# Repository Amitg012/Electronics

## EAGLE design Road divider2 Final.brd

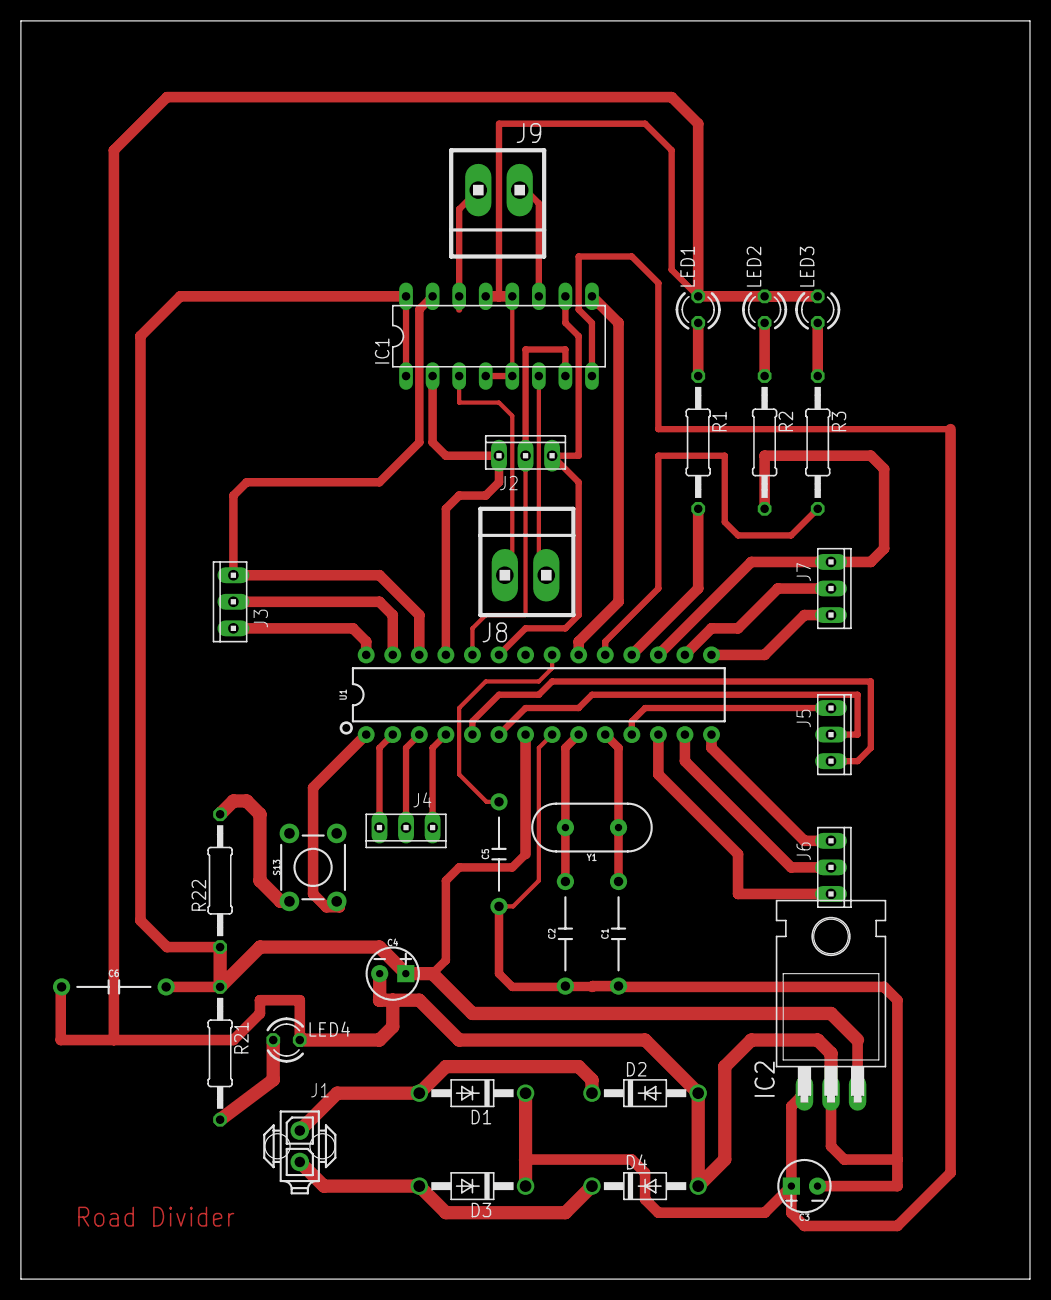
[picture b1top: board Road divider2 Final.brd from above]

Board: 2 copper layers, 96.5 x 120.3 mm, 33 parts (0 on the bottom side), 38 nets.

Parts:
C1, C2, C5, C6: 10nF; CAP-PTH-10MM
C3, C4: 10uF; CPOL-RADIAL-2.5MM-5MM-KIT
D1, D2, D3, D4: 1N4004; DO41-10
IC1: L293D; DIL16
IC2: 7812T; TO220H
J1: 794681-2
J2, J3, J4, J5, J6, J7: 10X03MTA
J8, J9: 1X2MTA
LED1, LED2, LED3, LED4: TLLR4400; LED3MM
R1, R2, R3, R21, R22: 0207/12
S13: MOMENTARY-SWITCH-SPST-PTH-6.0MM-KIT; TACTILE_SWITCH_PTH_6.0MM_KIT
U1: 328P; DIP28
Y1: 16MHz; HC49US

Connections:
5V: C4.1, C6.2, IC1.1, IC1.9, IC1.16, IC2.3, R21.1, R22.1, U1.7, U1.20
12V: C3.1, D1.C, D3.C, IC1.8, IC2.1
GND: C1.1, C2.1, C3.2, C4.2, C5.1, C6.1, D2.A, D4.A, IC1.4, IC1.5, IC1.12, IC1.13, IC2.2, LED1.K, LED2.K, LED3.K, LED4.K, U1.8, U1.22
unnamed: C5.2, U1.21
unnamed: D1.A, D2.C, J1.1
unnamed: C2.2, U1.9, Y1.2
unnamed: C1.2, U1.10, Y1.1
unnamed: LED4.A, R21.2
unnamed: R22.2, S13.1
unnamed: S13.3, U1.1
unnamed: D3.A, D4.C, J1.2
unnamed: IC1.2, J2.3, U1.25
unnamed: IC1.7, J2.2, U1.24
unnamed: IC1.10, J2.1, U1.23
unnamed: IC1.15, J3.1, U1.26
unnamed: J3.2, U1.27
unnamed: J3.3, U1.28
unnamed: J4.1, U1.2
unnamed: J4.2, U1.3
unnamed: J4.3, U1.4
unnamed: J5.1, U1.5
unnamed: J5.2, U1.6
unnamed: J5.3, U1.11
unnamed: J6.1, U1.12
unnamed: J6.2, U1.13
unnamed: J6.3, U1.14
unnamed: J7.1, U1.15
unnamed: J7.2, U1.16
unnamed: J7.3, R2.2, U1.17
unnamed: IC1.14, J9.1
unnamed: IC1.3, J8.2
unnamed: IC1.6, J8.1
unnamed: IC1.11, J9.2
unnamed: R1.2, U1.18
unnamed: R3.2, U1.19
unnamed: LED1.A, R1.1
unnamed: LED2.A, R2.1
unnamed: LED3.A, R3.1

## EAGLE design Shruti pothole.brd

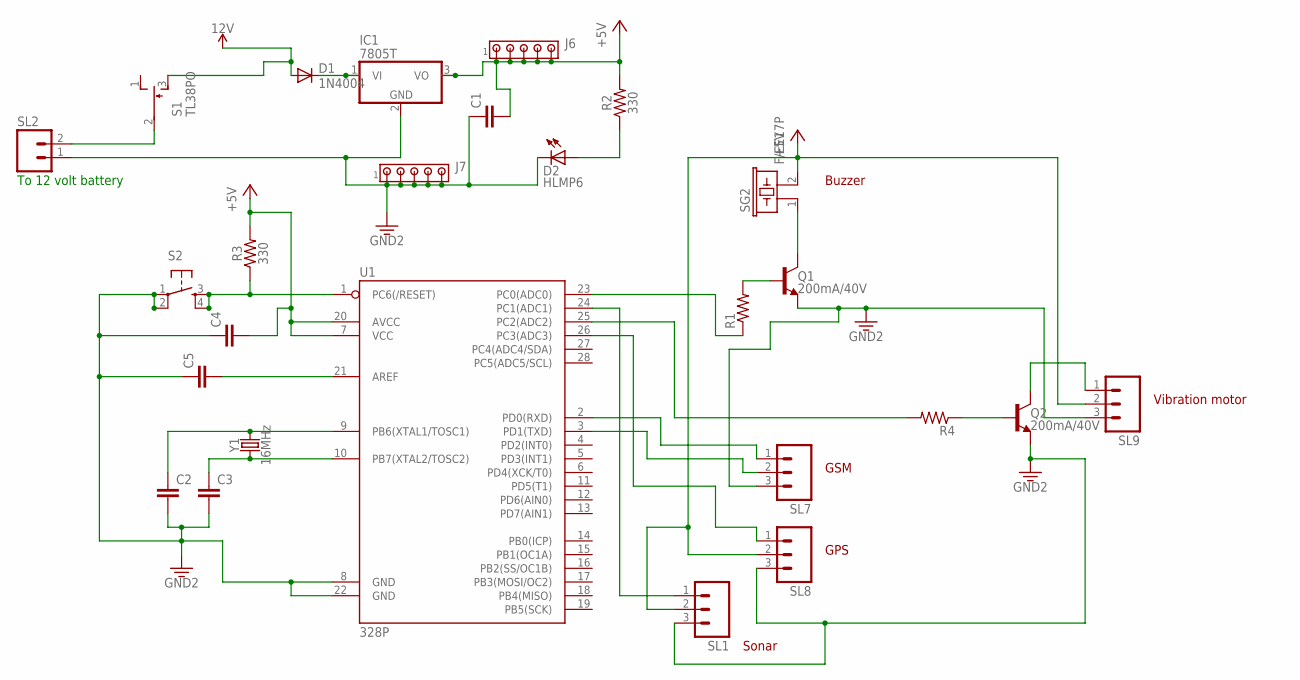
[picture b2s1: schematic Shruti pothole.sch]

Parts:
C1, C2, C3, C4, C5: C5/2.5; C5B2.5
D1: 1N4004; DO41-10
D2: HLMP6
IC1: 7805T; TO220H
J6, J7: MTA05-100; 10X05MTA
Q1, Q2: 200mA/40V; TO-92
R1, R4: R-US_0204/7; 0204/7
R2, R3: 330; AXIAL-0.3
S1: TL38PO; TL3XPO
S2: TAC_SWITCHPTH; TACTILE-PTH
SG2: F/EE17P
SL1, SL7, SL8, SL9: MA03; 03P
SL2: MA02; 02PA
U1: 328P; DIP28
Y1: 16MHz; HC49US

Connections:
3.3V: C1.1, C2.2, C3.2, C4.1, C5.1, D2.K, IC1.2 (GND), J7.1, J7.2, J7.3, J7.4, J7.5, Q1.1 (E), Q2.1 (E), S2.1, S2.2, SL1.3, SL2.1, SL7.3, SL8.3, SL9.3, U1.8 (GND), U1.22 (GND)
12V: D1.A, S1.3 (S)
+5V: C1.2, C4.2, IC1.3 (VO), J6.1, J6.2, J6.3, J6.4, J6.5, R2.P$2 (2), R3.P$2 (2), SG2.2, SL1.2, SL8.2, SL9.2, U1.7 (VCC), U1.20 (AVCC)
unnamed: Q1.3 (C), SG2.1
unnamed: SL7.1, U1.2 (PD0(RXD))
unnamed: Q1.2 (B), R1.2
unnamed: Q2.2 (B), R4.1
unnamed: SL7.2, U1.3 (PD1(TXD))
unnamed: R1.1, U1.23 (PC0(ADC0))
unnamed: D2.A, R2.P$1 (1)
unnamed: C3.1, U1.10 (PB7(XTAL2/TOSC2)), Y1.1
unnamed: SL1.1, U1.24 (PC1(ADC1))
unnamed: R3.P$1 (1), S2.3, S2.4, U1.1 (PC6(/RESET))
unnamed: R4.2, U1.25 (PC2(ADC2))
unnamed: C5.2, U1.21 (AREF)
unnamed: Q2.3 (C), SL9.1
unnamed: S1.2, SL2.2
unnamed: SL8.1, U1.26 (PC3(ADC3))
unnamed: D1.C, IC1.1 (VI)
unnamed: C2.1, U1.9 (PB6(XTAL1/TOSC1)), Y1.2

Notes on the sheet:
To 12 volt battery
Buzzer
Vibration motor
GSM
GPS
Sonar

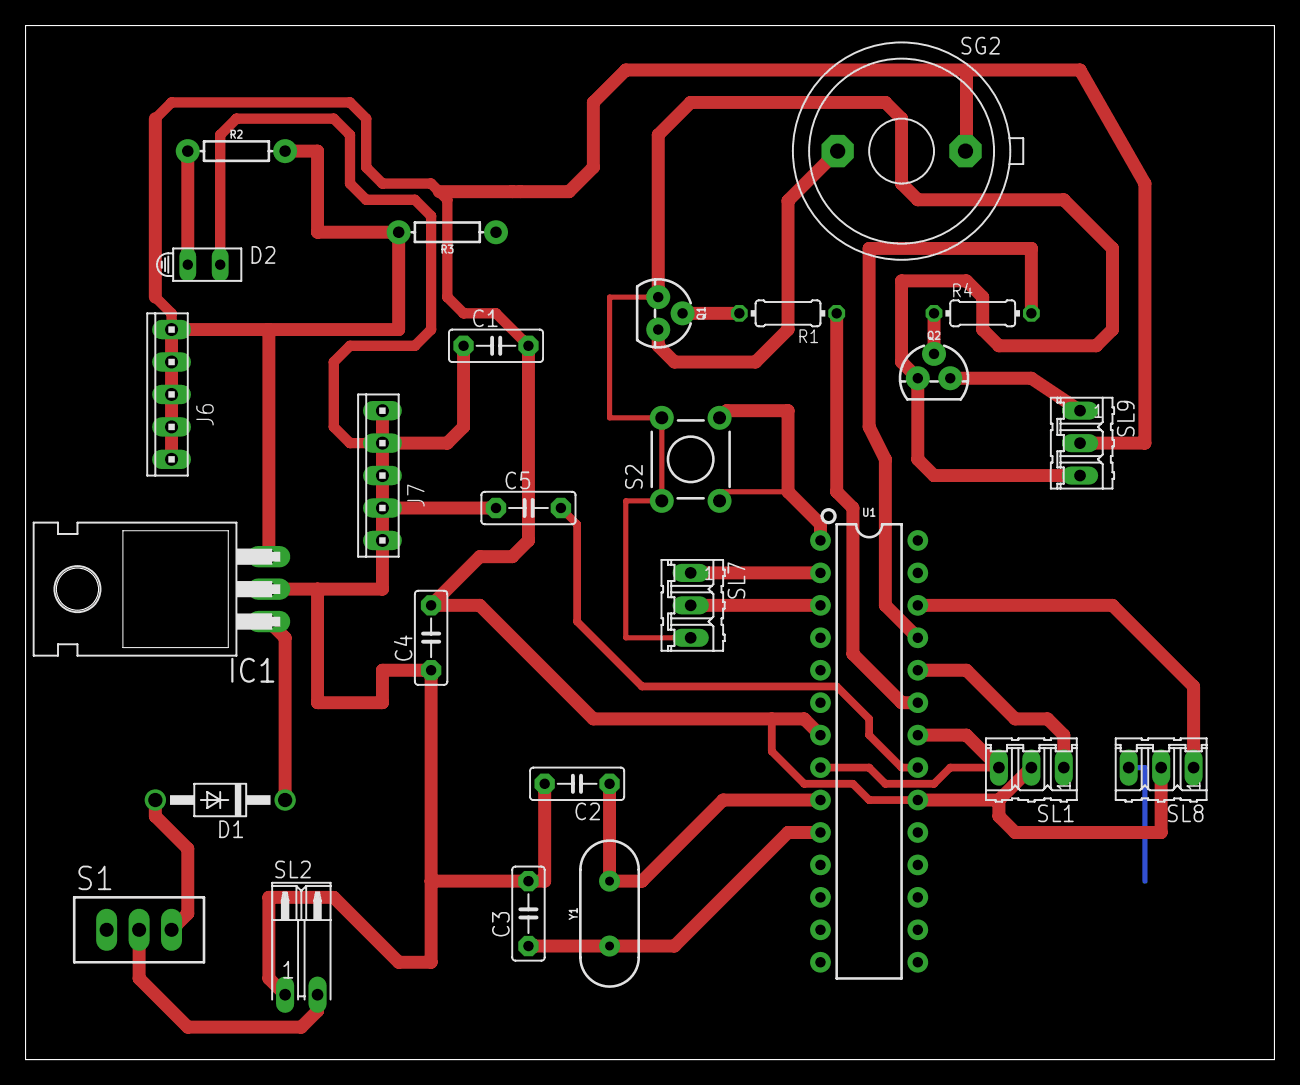
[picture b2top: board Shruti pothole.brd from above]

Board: 2 copper layers, 97.8 x 81.0 mm, 26 parts (0 on the bottom side), 20 nets.

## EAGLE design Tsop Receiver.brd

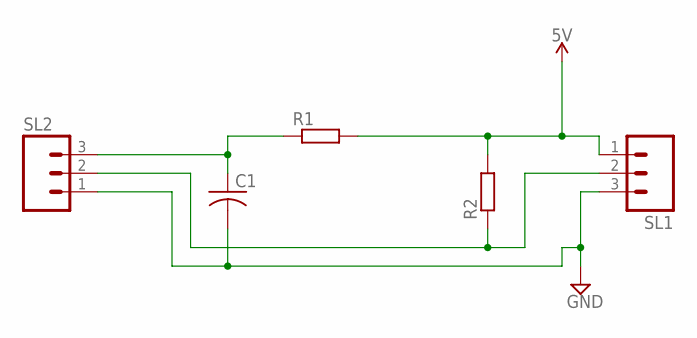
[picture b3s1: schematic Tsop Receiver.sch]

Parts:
C1: C-US025-024X044; C025-024X044
R1, R2: R0207/10; 0207/10
SL1, SL2: M03; 03P

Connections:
5V: R1.2, R2.2, SL1.1
GND: C1.2, SL1.3, SL2.1
unnamed: C1.1, R1.1, SL2.3
unnamed: R2.1, SL1.2, SL2.2

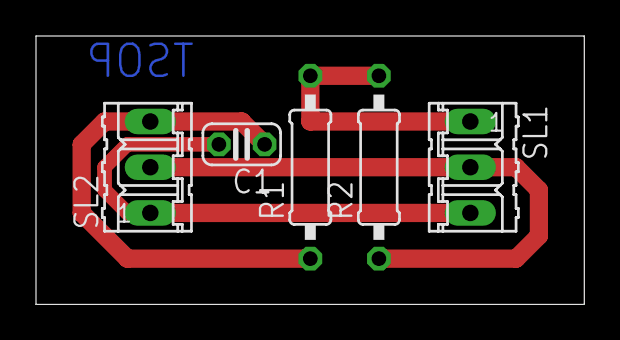
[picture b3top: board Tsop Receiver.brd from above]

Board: 2 copper layers, 30.5 x 14.9 mm, 5 parts (0 on the bottom side), 4 nets.

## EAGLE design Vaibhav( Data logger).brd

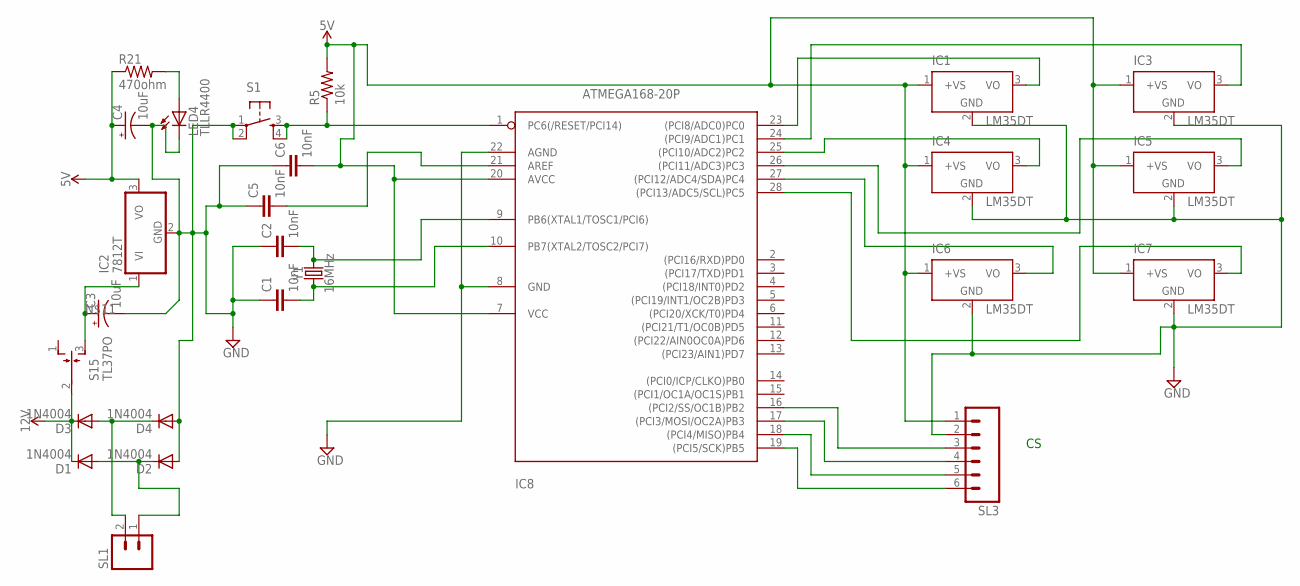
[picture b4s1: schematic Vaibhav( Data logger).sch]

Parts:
C1, C2, C5, C6: 10nF; CAP-PTH-10MM
C3, C4: 10uF; CPOL-RADIAL-2.5MM-5MM-KIT
D1, D2, D3, D4: 1N4004; DO41-10
IC1, IC3, IC4, IC5, IC6, IC7: LM35DT; TO220V
IC2: 7812T; TO220H
IC8: ATMEGA168-20P; DIL28-3
LED4: TLLR4400; LED3MM
R5: 10k; 0207/12
R21: 470ohm; 0207/12
S1: TAC_SWITCHPTH; TACTILE-PTH
S15: TL37PO; TL3XPO
SL1: MA02; 02PA
SL3: MA06; 06PA
Y1: 16MHz; HC49US

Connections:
5V: C4.1 (+), C6.2, IC1.1 (+VS), IC2.3 (VO), IC3.1 (+VS), IC4.1 (+VS), IC5.1 (+VS), IC6.1 (+VS), IC7.1 (+VS), IC8.7 (VCC), IC8.20 (AVCC), R5.2, R21.1, SL3.1
12V: D1.C, D3.C, S15.2
GND: C1.1, C2.1, C3.2 (-), C4.2 (-), C5.1, C6.1, D2.A, D4.A, IC1.2 (GND), IC2.2 (GND), IC3.2 (GND), IC4.2 (GND), IC5.2 (GND), IC6.2 (GND), IC7.2 (GND), IC8.8 (GND), IC8.22 (AGND), LED4.K (C), S1.1, S1.2, SL3.2
unnamed: IC1.3 (VO), IC8.23 ((PCI8/ADC0)PC0)
unnamed: IC3.3 (VO), IC8.24 ((PCI9/ADC1)PC1)
unnamed: C2.2, IC8.9 (PB6(XTAL1/TOSC1/PCI6)), Y1.2
unnamed: C1.2, IC8.10 (PB7(XTAL2/TOSC2/PCI7)), Y1.1
unnamed: LED4.A, R21.2
unnamed: C5.2, IC8.21 (AREF)
unnamed: IC4.3 (VO), IC8.25 ((PCI10/ADC2)PC2)
unnamed: IC5.3 (VO), IC8.26 ((PCI11/ADC3)PC3)
unnamed: IC8.1 (PC6(/RESET/PCI14)), R5.1, S1.3, S1.4
unnamed: D3.A, D4.C, SL1.2
unnamed: C3.1 (+), IC2.1 (VI), S15.3 (S)
unnamed: IC6.3 (VO), IC8.27 ((PCI12/ADC4/SDA)PC4)
unnamed: IC7.3 (VO), IC8.28 ((PCI13/ADC5/SCL)PC5)
unnamed: IC8.19 ((PCI5/SCK)PB5), SL3.6
unnamed: IC8.18 ((PCI4/MISO)PB4), SL3.5
unnamed: IC8.17 ((PCI3/MOSI/OC2A)PB3), SL3.4
unnamed: IC8.16 ((PCI2/SS/OC1B)PB2), SL3.3
unnamed: D1.A, D2.C, SL1.1

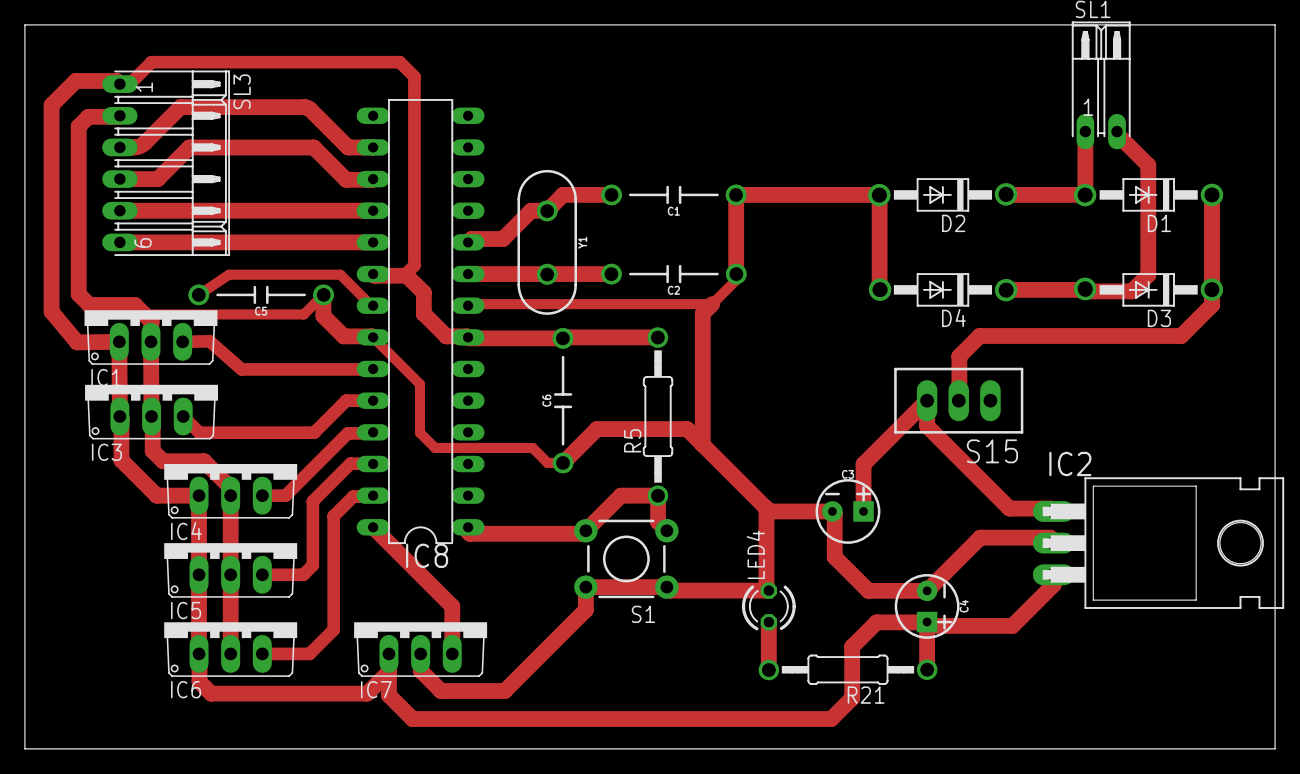
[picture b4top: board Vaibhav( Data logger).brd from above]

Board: 2 copper layers, 100.3 x 58.1 mm, 26 parts (0 on the bottom side), 21 nets.

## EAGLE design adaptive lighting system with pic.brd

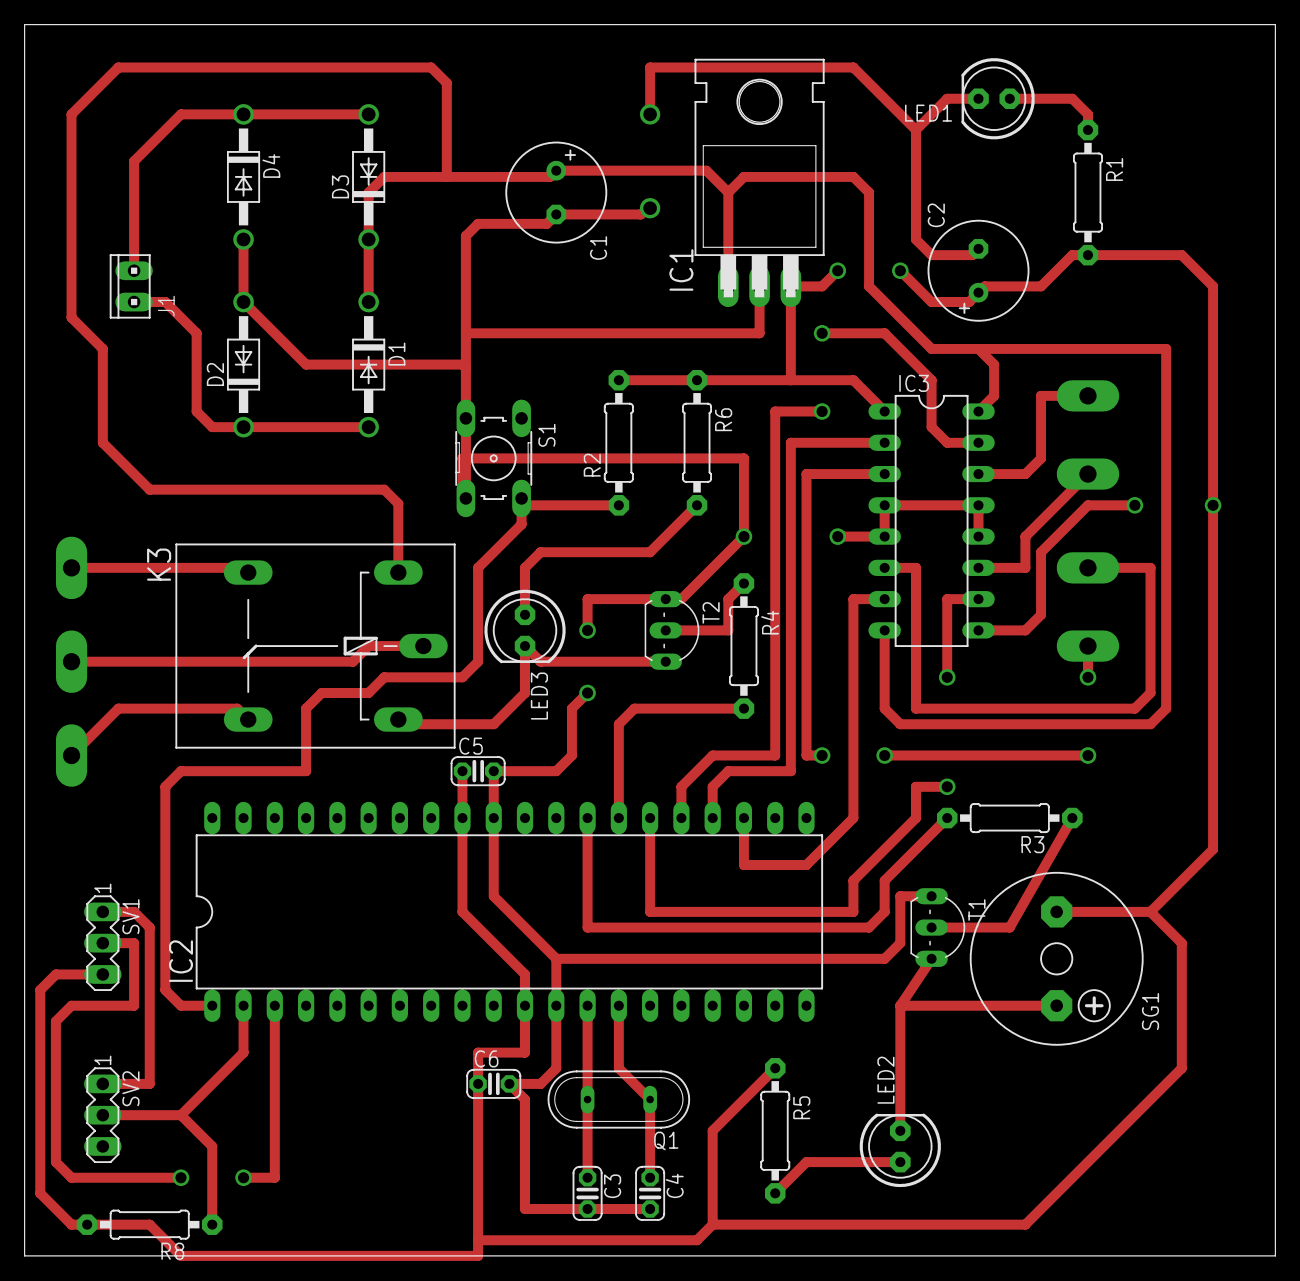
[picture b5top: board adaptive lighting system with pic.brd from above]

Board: 2 copper layers, 101.6 x 100.0 mm, 39 parts (0 on the bottom side), 30 nets.

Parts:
C1, C2: E3,5-8
C3, C4, C5, C6: C025-024X044
D1, D2, D3, D4: 1N4004; DO41-10
IC1: 7805T; TO220H
IC2: PIC18F4550_40; DIL40
IC3: L293D; DIL16
J1: 10X02MTA
JP1, JP2, JP3, JP4, JP8, JP9, JP10: 1X1-BIGPOGO
K3: G5L; G5LE
LED1, LED2, LED3: LED5MM
Q1: QS
R1: 0207/10
R2, R3, R4, R5, R6, R8: 10k; 0207/10
S1: B3F-10XX
SG1: F/CM12P
SV1, SV2: MA03-1
T1, T2: 2N2222; TO92-EBC-OVAL

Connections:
+5V: C2.+, C5.1, C6.1, IC1.3, IC2.11, IC2.32, IC3.1, IC3.9, R1.2, R2.2, R5.1, R6.1, R8.2, SG1.-, SV1.3
+12V: C1.+, D1.C, D3.C, IC1.1, IC3.8, IC3.16, K3.1
GND: C1.-, C2.-, C3.2, C4.2, C5.2, C6.2, D2.A, D4.A, IC1.2, IC2.12, IC2.31, IC3.4, IC3.5, IC3.12, IC3.13, LED1.K, S1.3, S1.4, SV1.1, SV2.1, T1.E, T2.E
unnamed: D1.A, D2.C, J1.2
unnamed: D3.A, D4.C, J1.1
unnamed: C4.1, IC2.14, Q1.1
unnamed: C3.1, IC2.13, Q1.2
unnamed: LED1.A, R1.1
unnamed: LED2.A, R5.2
unnamed: IC2.2, R8.1, SV2.2
unnamed: IC2.3, SV1.2
unnamed: R3.1, T1.B
unnamed: IC2.1, R2.1, S1.2
unnamed: R4.1, T2.B
unnamed: LED2.K, SG1.+, T1.C
unnamed: K3.2, LED3.K, T2.C
unnamed: LED3.A, R6.2
unnamed: JP4.P$1, K3.P
unnamed: JP2.P$1, K3.O
unnamed: JP3.P$1, K3.S
unnamed: IC3.3, JP1.P$1
unnamed: IC3.6, JP8.P$1
unnamed: IC3.14, JP9.P$1
unnamed: IC3.11, JP10.P$1
unnamed: IC2.24, IC3.2
unnamed: IC2.25, IC3.15
unnamed: IC2.23, IC3.7
unnamed: IC2.26, IC3.10
unnamed: IC2.27, R4.2
unnamed: IC2.28, R3.2

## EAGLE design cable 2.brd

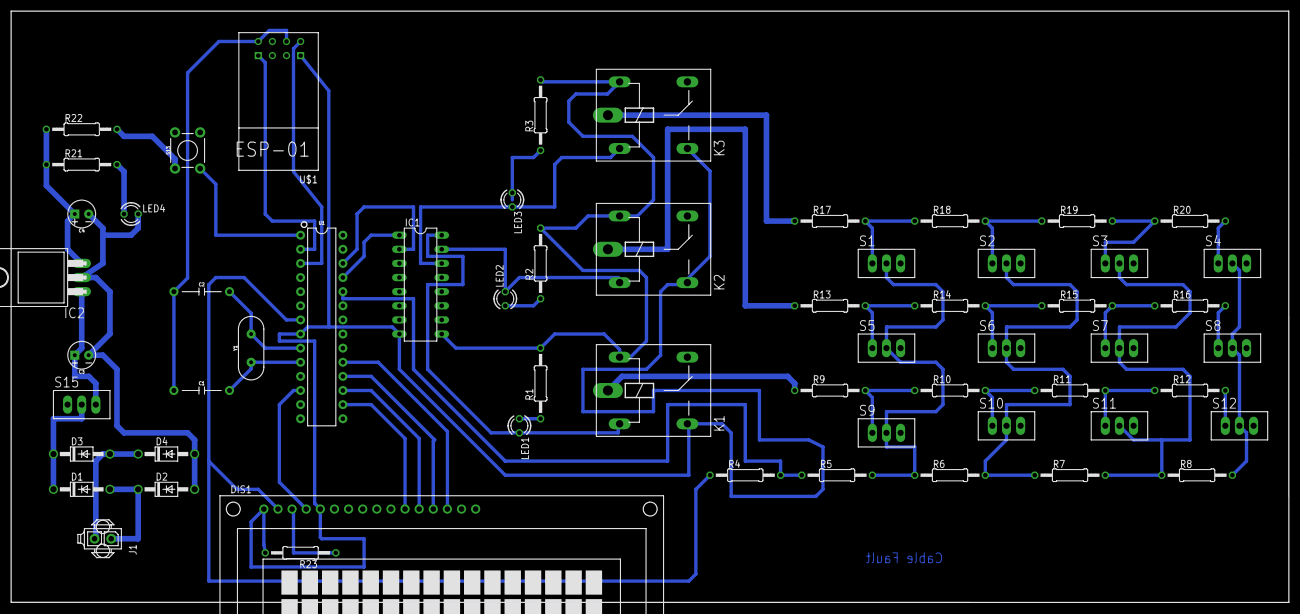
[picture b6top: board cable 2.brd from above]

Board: 2 copper layers, 229.9 x 106.4 mm, 59 parts (0 on the bottom side), 51 nets.

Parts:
C1, C2: 10nF; CAP-PTH-10MM
C3, C4: 10uF; CPOL-RADIAL-2.5MM-5MM-KIT
D1, D2, D3, D4: 1N4004; DO41-10
DIS1: TUXGR_16X2_R2
IC1: ULN2004AN; DIL16
IC2: 7812T; TO220H
J1: 794681-2
K1, K2, K3: ZF112
LED1, LED2, LED3, LED4: TLLR4400; LED3MM
R1, R2, R3, R4, R5, R6, R7, R8, R9, R10, R11, R12, R13, R14, R15, R16, R17, R18, R19, R20, R21, R22, R23: 0207/12
S1, S2, S3, S4, S5, S6, S7, S8, S9, S10, S11, S12: TL36PO; TL3XPO
S13: MOMENTARY-SWITCH-SPST-PTH-6.0MM-KIT; TACTILE_SWITCH_PTH_6.0MM_KIT
S15: TL37PO; TL3XPO
U1: 328P; DIP28
U$1: ESP01
Y1: 16MHz; HC49US

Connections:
3.3V: C1.1, C2.1, U$1.CH_PD, U$1.VCC
5V: DIS1.2, R4.1, U1.7
12V: IC1.9, K1.1, K2.1, K3.1, R1.2, R2.2, R3.2
GND: DIS1.1, DIS1.5, IC1.8, K1.S, K2.S, K3.S, R23.2, U1.8, U$1.GND
unnamed: DIS1.3, R23.1
unnamed: R16.2, S8.1
unnamed: C2.2, U1.9, Y1.2
unnamed: C1.2, U1.10, Y1.1
unnamed: LED4.A, R21.2
unnamed: C3.2, C4.2, D2.A, D4.A, IC2.2, LED4.K
unnamed: C4.1, IC2.3, R21.1, R22.1
unnamed: R22.2, S13.1
unnamed: S13.3, U1.1
unnamed: D3.A, D4.C, J1.2
unnamed: C3.1, IC2.1, S15.3
unnamed: U1.3, U$1.TX
unnamed: DIS1.11, U1.16
unnamed: DIS1.12, U1.17
unnamed: DIS1.13, U1.18
unnamed: U1.2, U$1.RX
unnamed: DIS1.14, U1.19
unnamed: DIS1.4, U1.12
unnamed: LED1.A, R1.1
unnamed: IC1.16, K1.2, LED1.K
unnamed: IC1.15, K2.2, LED2.K
unnamed: LED2.A, R2.1
unnamed: IC1.14, K3.2, LED3.K
unnamed: LED3.A, R3.1
unnamed: IC1.1, U1.25
unnamed: IC1.2, U1.26
unnamed: K1.P, R9.1
unnamed: R4.2, R5.1, U1.24
unnamed: R8.2, S4.2, S8.2, S12.2
unnamed: R5.2, R6.1, S1.2, S5.2, S9.2
unnamed: K2.P, R13.1
unnamed: K3.P, R17.1
unnamed: R17.2, R18.1, S1.1
unnamed: R18.2, R19.1, S2.1
unnamed: R19.2, R20.1, S3.1
unnamed: R13.2, R14.1, S5.1
unnamed: R14.2, R15.1, S6.1
unnamed: R15.2, R16.1, S7.1
unnamed: R9.2, R10.1, S9.1
unnamed: R10.2, R11.1, S10.1
unnamed: R11.2, R12.1, S11.1
unnamed: R6.2, R7.1, S2.2, S6.2, S10.2
unnamed: R7.2, R8.1, S3.2, S7.2, S11.2
unnamed: R20.2, S4.1
unnamed: R12.2, S12.1
unnamed: D1.C, D3.C, S15.2
unnamed: D1.A, D2.C, J1.1

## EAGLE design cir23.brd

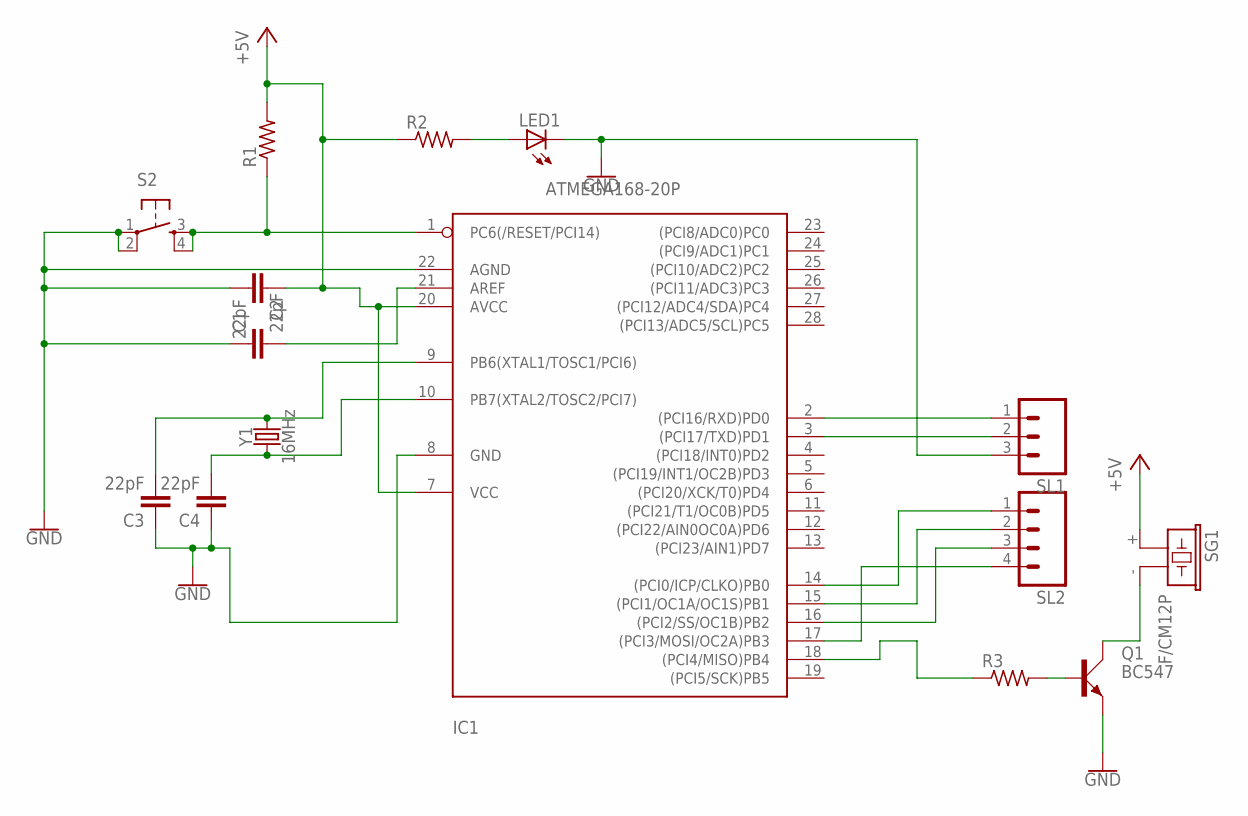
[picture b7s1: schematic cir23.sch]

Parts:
C1, C2, C3, C4: 22pF; CAP-PTH-2.54
IC1: ATMEGA168-20P; DIL28-3
LED1: LED_ELD260; LED_LD260
Q1: BC547; SOT54A
R1, R2, R3: R-US_0204/7; 0204/7
S2: TAC_SWITCHPTH; TACTILE-PTH
SG1: F/CM12P
SL1: MA03; 03P
SL2: MA04; 04PA
Y1: 16MHz; HC49US

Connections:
+5V: C2.1, IC1.7 (VCC), IC1.20 (AVCC), R1.2, R2.1, SG1.+ (1)
GND: C1.1, C2.2, C3.1, C4.1, IC1.8 (GND), IC1.22 (AGND), LED1.K (C), Q1.E, S2.1, S2.2, SL1.3
unnamed: IC1.1 (PC6(/RESET/PCI14)), R1.1, S2.3, S2.4
unnamed: IC1.14 ((PCI0/ICP/CLKO)PB0), SL2.1
unnamed: C1.2, IC1.21 (AREF)
unnamed: C3.2, IC1.9 (PB6(XTAL1/TOSC1/PCI6)), Y1.2
unnamed: C4.2, IC1.10 (PB7(XTAL2/TOSC2/PCI7)), Y1.1
unnamed: IC1.15 ((PCI1/OC1A/OC1S)PB1), SL2.2
unnamed: IC1.16 ((PCI2/SS/OC1B)PB2), SL2.3
unnamed: IC1.17 ((PCI3/MOSI/OC2A)PB3), SL2.4
unnamed: IC1.18 ((PCI4/MISO)PB4), R3.1
unnamed: LED1.A, R2.2
unnamed: IC1.2 ((PCI16/RXD)PD0), SL1.1
unnamed: IC1.3 ((PCI17/TXD)PD1), SL1.2
unnamed: Q1.B, R3.2
unnamed: Q1.C, SG1.- (2)

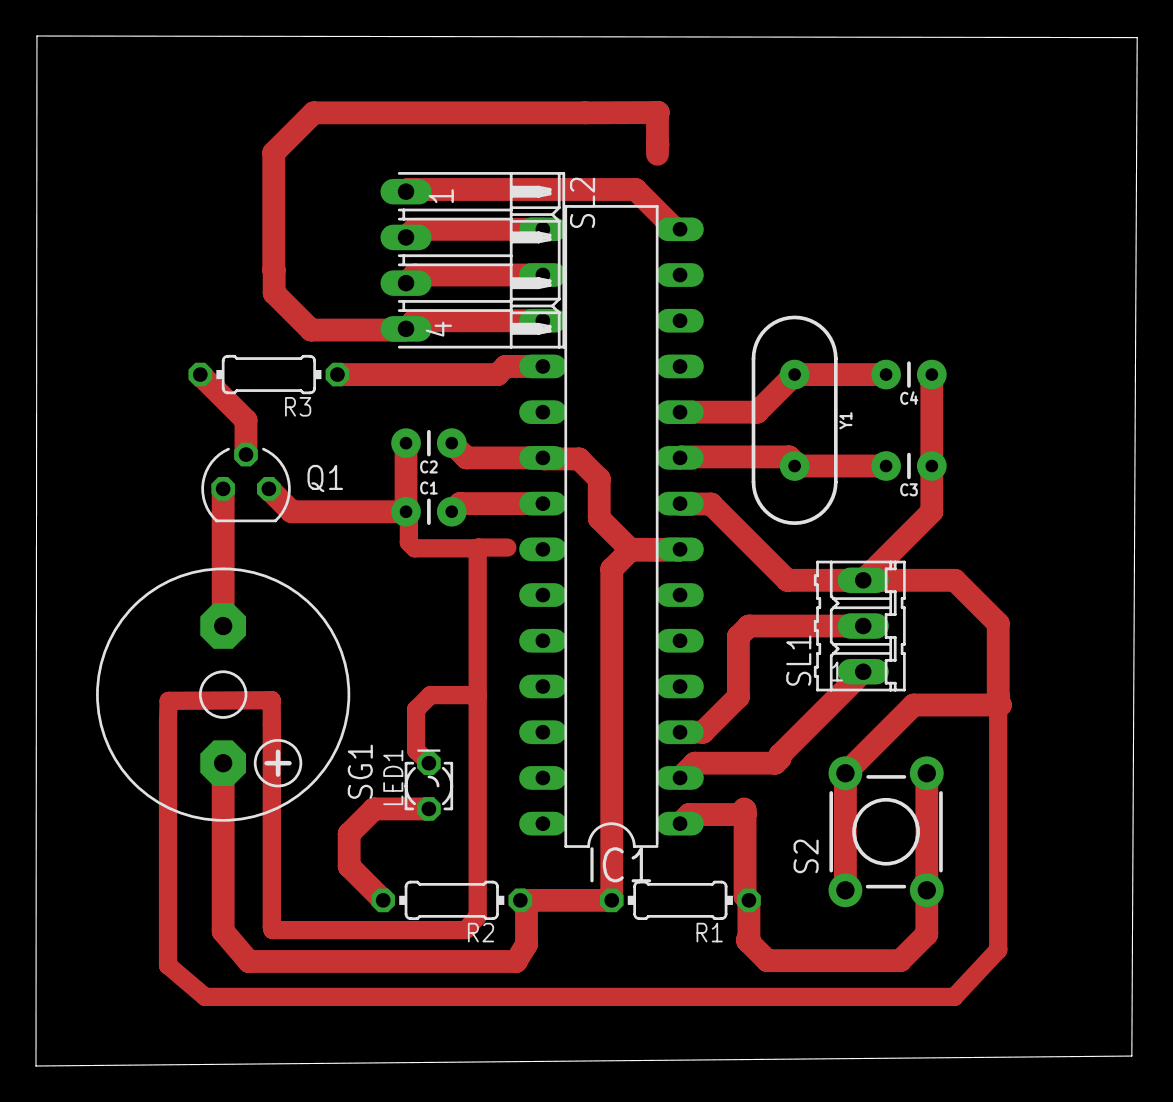
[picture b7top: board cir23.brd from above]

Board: 2 copper layers, 61.2 x 57.2 mm, 15 parts (0 on the bottom side), 16 nets.

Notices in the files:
parts and their libraries:
SparkFun-Capacitors: Licensing: Creative Commons ShareAlike 4.0 International - https://creativecommons.org/licenses/by-sa/4.0
